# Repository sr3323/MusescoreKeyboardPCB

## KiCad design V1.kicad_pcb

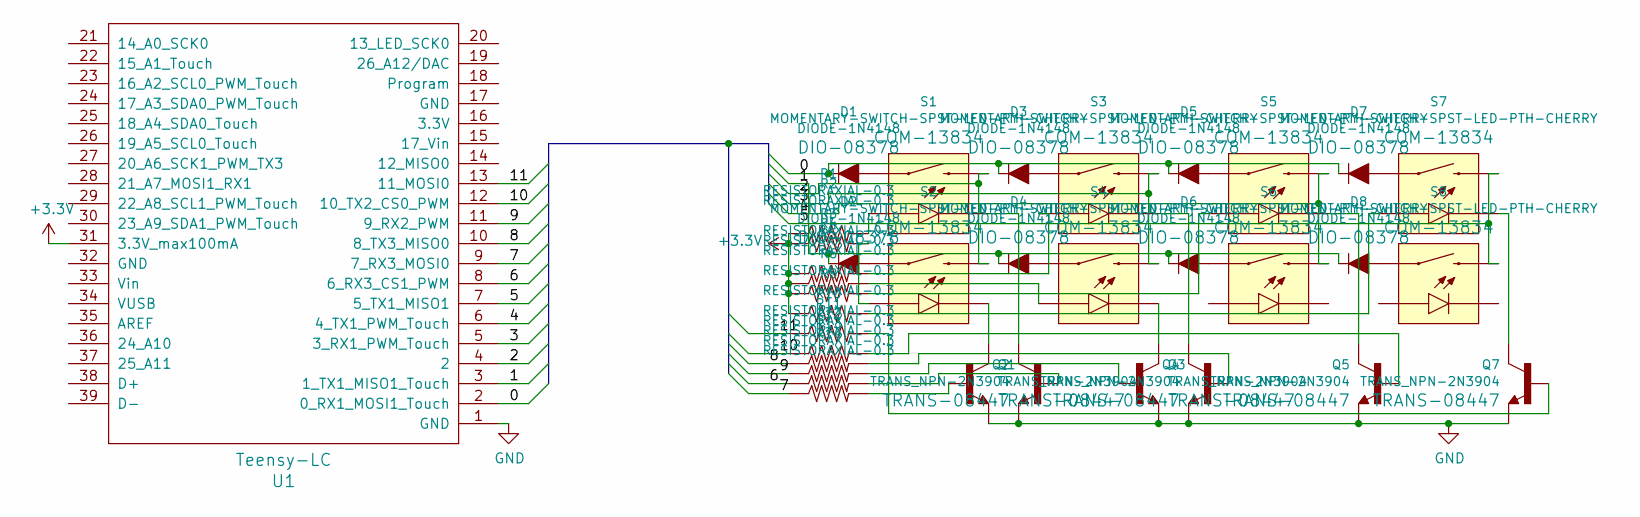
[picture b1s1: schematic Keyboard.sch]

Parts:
D1, D2, D3, D4, D5, D6, D7, D8: DIODE-1N4148; DIODE-1N4148-KIT
Q1, Q2, Q3, Q4, Q5, Q7: TRANS_NPN-2N3904; TO-92-AMMO
R1, R2, R3, R4, R5, R6, R8, R10, R11, R12, R13, R14: RESISTORAXIAL-0.3; AXIAL-0.3-KIT
S1, S2, S3, S4, S5, S6, S7, S8: MOMENTARY-SWITCH-SPST-LED-PTH-CHERRY; CHERRY-MX-LED
U1: Teensy-LC; Teensy30_31_32_LC

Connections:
+3V3: R1.P$1 (1), R2.P$1 (1), R3.P$1 (1), R4.P$1 (1), R5.P$1 (1), R6.P$1 (1), U1.31 (3.3V_max100mA)
/0: D1.C, D3.C, D5.C, D7.C, U1.2 (0_RX1_MOSI1_Touch)
/1: D2.C, D4.C, D6.C, D8.C, U1.3 (1_TX1_MISO1_Touch)
/2: S1.S2 (2), S2.S2 (2), U1.4 (2)
/3: S3.S2 (2), S4.S2 (2), U1.5 (3_RX1_PWM_Touch)
/4: S5.S2 (2), S6.S2 (2), U1.6 (4_TX1_PWM_Touch)
/5: S7.S2 (2), S8.S2 (2), U1.7 (5_TX1_MISO1)
/6: R13.P$1 (1), U1.8 (6_RX3_CS1_PWM)
/7: R14.P$1 (1), U1.9 (7_RX3_MOSI0)
/8: R11.P$1 (1), U1.10 (8_TX3_MISO0)
/9: R12.P$1 (1), U1.11 (9_RX2_PWM)
/10: R10.P$1 (1), U1.12 (10_TX2_CS0_PWM)
/11: R8.P$1 (1), U1.13 (11_MOSI0)
GND: Q1.1 (E), Q2.1 (E), Q3.1 (E), Q4.1 (E), Q5.1 (E), Q7.1 (E), U1.1 (GND)
unnamed: D1.A, S1.S1 (1)
unnamed: D2.A, S2.S1 (1)
unnamed: D3.A, S3.S1 (1)
unnamed: D4.A, S4.S1 (1)
unnamed: D5.A, S5.S1 (1)
unnamed: D6.A, S6.S1 (1)
unnamed: D7.A, S7.S1 (1)
unnamed: D8.A, S8.S1 (1)
unnamed: Q1.2 (B), R14.P$2 (2)
unnamed: Q1.3 (C), S2.K (C)
unnamed: Q2.2 (B), R13.P$2 (2)
unnamed: Q2.3 (C), S1.K (C)
unnamed: Q3.2 (B), R12.P$2 (2)
unnamed: Q3.3 (C), S4.K (C)
unnamed: Q4.2 (B), R11.P$2 (2)
unnamed: Q4.3 (C), S3.K (C)
unnamed: Q5.2 (B), R10.P$2 (2)
unnamed: Q5.3 (C), S5.K (C)
unnamed: Q7.2 (B), R8.P$2 (2)
unnamed: Q7.3 (C), S7.K (C)
unnamed: R1.P$2 (2), S1.A
unnamed: R2.P$2 (2), S2.A
unnamed: R3.P$2 (2), S3.A
unnamed: R4.P$2 (2), S4.A
unnamed: R5.P$2 (2), S5.A
unnamed: R6.P$2 (2), S7.A

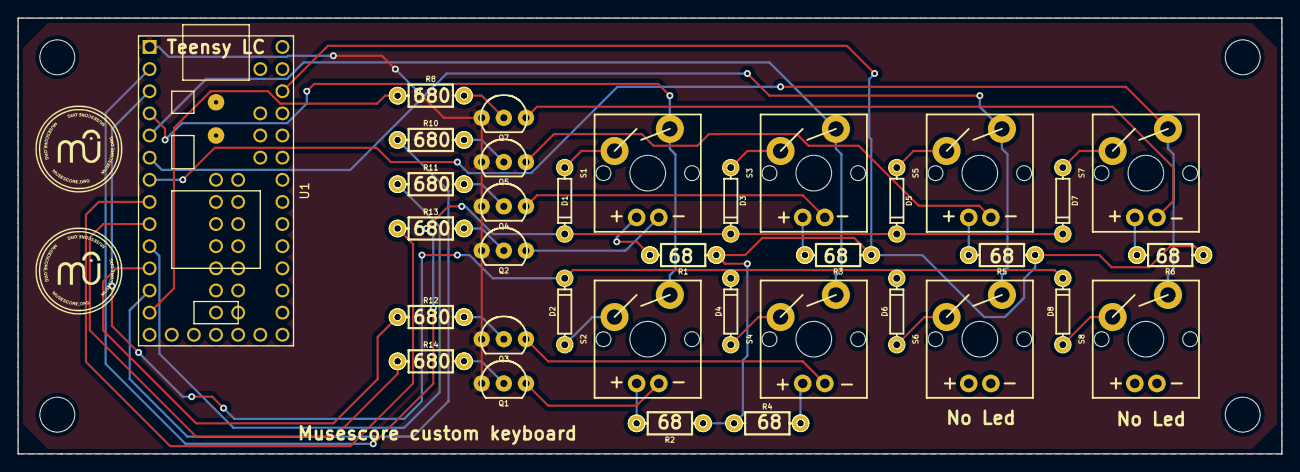
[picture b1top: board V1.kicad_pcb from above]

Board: 2 copper layers, 145.0 x 50.0 mm, 35 parts (0 on the bottom side), 40 nets.
